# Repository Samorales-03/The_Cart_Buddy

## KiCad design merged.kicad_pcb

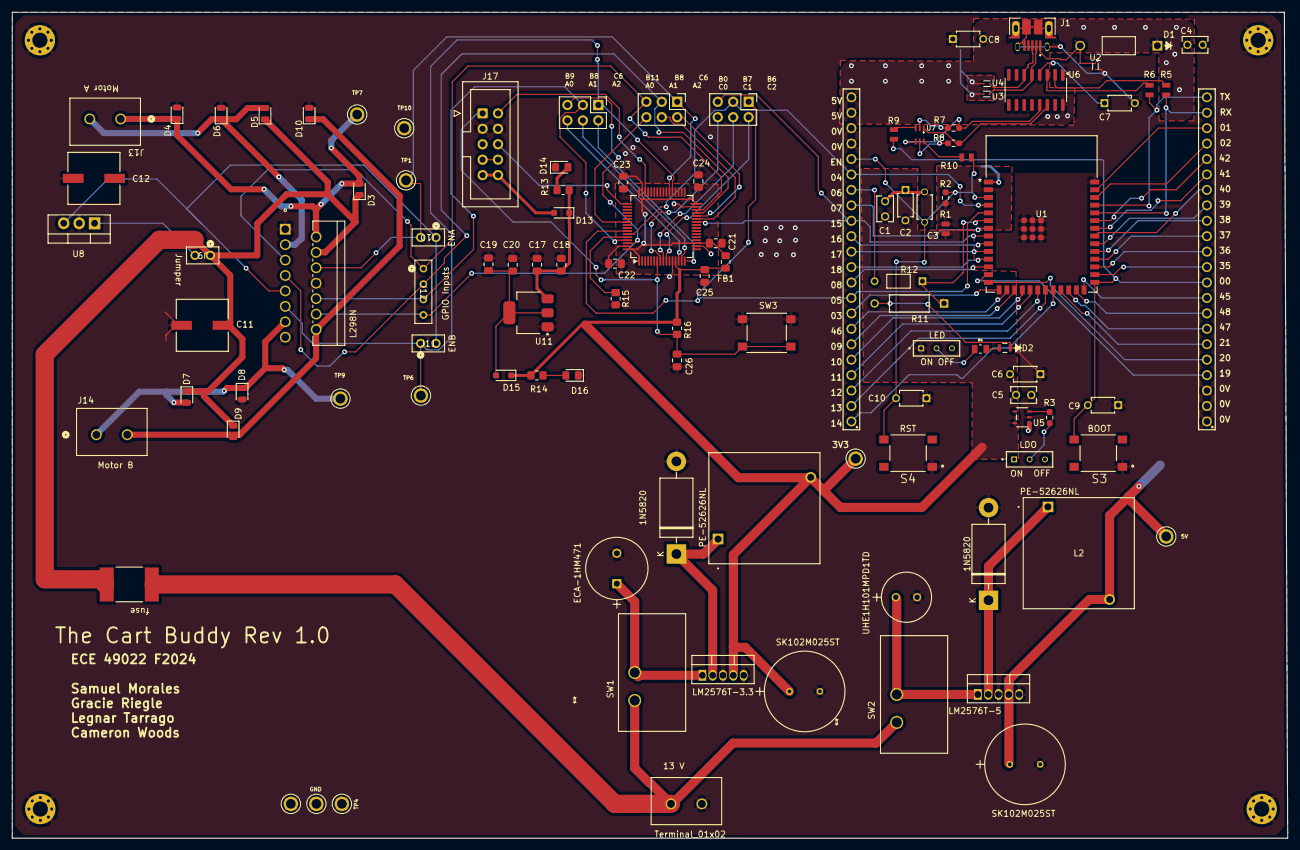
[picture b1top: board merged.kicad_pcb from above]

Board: 2 copper layers, 209.9 x 135.9 mm, 110 parts (0 on the bottom side), 96 nets.

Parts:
C1, C4, C5: 10uF; CAP_FG18_TDK
C2, C6, C7, C8, C9, C10: 0.1uF; K104K10X7RF5UH5_VIS
C3: 1uF; CAPRB500W50L400T250H550
C11, C12: 220 uF; CAP_PC_8X12_NCH
C13: ECA-1HM471; PCAP_10x20_PAN
C14, C16: SK102M025ST; SK102M025ST_CND
C15: UHE1H101MPD1TD; CAP_RN_8X11P5_NCH
C17, C20: 22uF; C_0805_2012Metric_Pad1.18x1.45mm_HandSolder
C18, C19, C21, C22, C23, C24, C25, C26: 0.1uF; C_0805_2012Metric_Pad1.18x1.45mm_HandSolder
CR1: L298N; Multiwatt15_V_STM
D1: 1N5819; CR_DO-41_SDS
D2: LED-red; LED0805N_CML-L
D3, D4, D5, D6, D7, D8, D9, D10: D_0805_2012Metric
D11, D12: 1N5820; D_DO-201AD_P15.24mm_Horizontal
D13, D15: BAT60JFILM; D_SOD-323_HandSoldering
D14, D16: LED; LED_0805_2012Metric_Pad1.15x1.40mm_HandSolder
F1: fuse; 0ZCF_BEL
FB1: FerriteBead; L_0805_2012Metric_Pad1.15x1.40mm_HandSolder
H1, H2, H3, H4: MountingHole_2.5mm_Pad_Via
J1: Micro-USB; AMPHENOL_10103594-0001LF
J2: ON; SAMTEC_TS-103-T-A
J3: LDO; SAMTEC_TS-103-T-A
J4, J5, J16: Conn_02x03_Odd_Even; PinHeader_2x03_P2.54mm_Vertical
J6: LEFT; 61302211121
J7: RIGHT; 61302211121
J9: Jumper; CON2_1X2_TUC_HTS_SAI
J10: ENA; CON2_1X2_TUC_HTS_SAI
J11: ENB; CON2_1X2_TUC_HTS_SAI
J12: GPIO Inputs; CON4_1X4_TU_HTS_SAI
J13: Motor A; CONN_OSTTC022162_OST
J14: Motor B; CONN_OSTTC022162_OST
J15: Terminal_01x02; CONN_OSTTC022162_OST
J17: Conn_02x05_Odd_Even; IDC-Header_2x05_P2.54mm_Vertical
L1, L2: PE-52626NL; IND_PE-526_LOWPROFILE_PUL
R1, R5, R6, R9, R10: 0Ohm; RES_CRCW_0805_VIS-L
R2, R3, R7, R8: 10kOhm; R_0603_1608Metric_Pad0.98x0.95mm_HandSolder
R4: 68Ohm; RESC2012X60N
R11: 3kOhm; STA_CF14_STP
R12: 2kOhm; STA_CF18_STP
R13, R16: 5.1k; R_0805_2012Metric_Pad1.20x1.40mm_HandSolder
R14: 1k; R_0805_2012Metric_Pad1.20x1.40mm_HandSolder
R15: 100k; R_0805_2012Metric_Pad1.20x1.40mm_HandSolder
S3, S4: SW; SW_PTS645SK50SMTR92LFS
SW1, SW2: L101011MS02Q; SW_1MS02Q_CNK
SW3: SW_Push; SW_SPST_PTS645
TP1, TP2, TP3, TP4, TP5, TP6, TP7, TP8, TP9, TP10: 5006; KEYSTONE_5006
U1: ESP32-S3-WROOM-1-N8; ESP32-S3-WROOM-1_EXP
U2, U3, U4: ESD; CPDQ-L
U5: LDO; SOT-25_TOR-L
U6: CH340C; SOIC-16_3.9x9.9mm_P1.27mm
U7: BJT; SOT236
U8: L7805; TO-220-3_Vertical
U9: LM2576T-3.3; TO-220-5_Vertical
U10: LM2576T-5; TO-220-5_Vertical
U11: LD1117S33TR_SOT223; SOT-223-3_TabPin2
U12: STM32F091R_B-C_Tx; LQFP-64_10x10mm_P0.5mm

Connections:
+5V: C17.1, C18.1, D13.1, R13.1, U11.3 (VI)
/DTR: R7.1, U6.13 (~DTR), U7.4
/EN: C3.2, C10.2, J6.18, R2.2, R10.2, S4.4, U1.3 (EN)
/ESP_3V3: R1.2, R2.1, U1.2 (3V3)
/GPIO00: C9.2, J7.10, R9.1, S3.4, U1.27 (IO0)
/GPIO01: J7.20, U1.39 (IO1)
/GPIO02: J7.19, U1.38 (IO2)
/GPIO03: J6.8, U1.15 (IO3)
/GPIO06: R11.1, R12.1, U1.6 (IO6)
/GPIO07: J6.15, U1.7 (IO7)
/GPIO08: J6.10, U1.12 (IO8)
/GPIO09: J6.6, U1.17 (IO9)
/GPIO10: J6.5, U1.18 (IO10)
/GPIO11: J6.4, U1.19 (IO11)
/GPIO12: J6.3, U1.20 (IO12)
/GPIO13: J6.2, U1.21 (IO13)
/GPIO14: J6.1, U1.22 (IO14)
/GPIO16: J6.13, U1.9 (IO16)
/GPIO17: J6.12, U1.10 (IO17)
/GPIO18: J6.11, U1.11 (IO18)
/GPIO19: J7.4, U1.13 (IO19)
/GPIO20: J7.5, U1.14 (IO20)
/GPIO21: J7.6, U1.23 (IO21)
/GPIO35: J7.11, U1.28 (IO35)
/GPIO36: J7.12, U1.29 (IO36)
/GPIO37: J7.13, U1.30 (IO37)
/GPIO38: J7.14, U1.31 (IO38)
/GPIO39: J7.15, U1.32 (IO39)
/GPIO40: J7.16, U1.33 (IO40)
/GPIO41: J7.17, U1.34 (IO41)
/GPIO42: J7.18, U1.35 (IO42)
/GPIO45: J7.9, U1.26 (IO45)
/GPIO46: J6.7, U1.16 (IO46)
/GPIO47: J7.7, U1.24 (IO47)
/GPIO48: J7.8, U1.25 (IO48)
/MOTORA: CR1.2 (OUTPUT_1), D3.2 (A), D4.1 (K), J13.1, TP7.1
/MOTORB: CR1.13 (OUTPUT_3), D7.2 (A), D8.1 (K), J14.1, TP9.1
/RTS: R8.2, U6.14 (~RTS), U7.1
/STM_3V3: C21.1, C22.1, C23.1, C24.1, FB1.1, U12.1 (VBAT), U12.19 (VDD), U12.32 (VDD), U12.48 (VDDIO2), U12.64 (VDD)
/U0RXD: J7.21, R5.2, U1.36 (RXD0)
/U0TXD: J7.22, R6.2, U1.37 (TXD0)
/USB_DN: J1.2 (D-), U3.1, U6.5 (UD+)
/USB_DP: J1.3 (D+), U4.1, U6.6 (UD-)
/VBUS: D1.2, J1.1 (VCC), U2.1
/VCC_3V3: C1.2, C2.2, C5.2, C6.2, C14.1, C25.1, D15.1, FB1.2, J2.01, L1.2, R1.1, R14.1, R16.1, TP2.1, U5.5 (VOUT), U9.4 (FB), U12.13 (VDDA)
/VCC_5V: C4.2, C8.2, C16.1, D1.1, J3.01, J6.21, J6.22, L2.2, TP5.1, U5.1 (VIN), U6.16 (VCC), U10.4 (FB)
/VCC_13V: F1.1, J15.1, SW1.1, SW2.1
/VCC_13V_FUSE: C11.1, CR1.4 (SUPPLY_VOLTAGE_VS), D3.1 (K), D5.1 (K), D7.1 (K), D9.1 (K), F1.2, J9.1
Earth: C1.1, C2.1, C3.1, C4.1, C5.1, C6.1, C7.2, C8.1, C9.1, C10.1, C11.2, C12.2, C13.2, C14.2, C15.2, C16.2, C17.2, C18.2, C19.2, C20.2, C21.2, C22.2, C23.2, C24.2, C25.2, C26.2, CR1.1 (CURRENT_SENSING_A), CR1.8 (GND), CR1.15 (CURRENT_SENSING_B), D2.1 (K), D4.2 (A), D6.2 (A), D8.2 (A), D10.2 (A), D11.2 (A), D12.2 (A), D14.1 (K), D16.1 (K), H1.1, H2.1, H3.1, H4.1, J1.5 (GND), J1.6 (SHIELD), J1.7 (SHIELD__1), J1.8 (SHIELD__2), J1.9 (SHIELD__3), J1.10 (SHIELD__4), J1.11 (SHIELD__5), J1.S1 (SHIELD__6), J1.S2 (SHIELD__7), J6.19, J6.20, J7.1, J7.2, J7.3, J15.2, J17.3, J17.4, R11.2, R15.2, S3.1, S4.1, SW3.1, TP3.1, TP4.1, TP8.1, TP10.1, U1.1 (GND), U1.40 (GND), U1.41 (GND), U1.42 (GND), U1.43 (GND), U1.44 (GND), U1.45 (GND), U1.46 (GND), U1.47 (GND), U1.48 (GND), U1.49 (GND), U2.2, U3.2, U4.2, U5.2 (VSS), U6.1 (GND), U8.2 (GND), U9.3 (GND), U9.5 (~ON/OFF), U10.3 (GND), U10.5 (~ON/OFF), U11.1 (GND), U12.12 (VSSA), U12.18 (VSS), U12.31 (VSS), U12.47 (VSS), U12.63 (VSS)
NRST: C26.1, J17.1, R16.2, SW3.2, U12.7 (NRST)
unnamed: C12.1, CR1.9 (LOGIC_SUPPLY_VOLTAGE_VSS), J10.1, J11.2, U8.3 (OUT)
unnamed: CR1.3 (OUTPUT_2), D5.2 (A), D6.1 (K), J13.2
unnamed: CR1.14 (OUTPUT_4), D9.2 (A), D10.1 (K), J14.2
unnamed: D2.2 (A), R4.1
unnamed: D11.1 (K), L1.1, U9.2 (OUT)
unnamed: D12.1 (K), L2.1, U10.2 (OUT)
unnamed: D14.2 (A), R13.2
unnamed: D16.2 (A), R14.2
unnamed: J2.02, R4.2
unnamed: J3.02, R3.1
unnamed: J6.16, R12.2
unnamed: R7.2, U7.2
unnamed: R8.1, U7.5
unnamed: R9.2, U7.3
unnamed: R10.1, U7.6
unnamed: R3.2, U5.3 (CE)
unnamed: R6.1, U6.3 (RXD)
unnamed: R5.1, U6.2 (TXD)
unnamed: C7.1, U6.4 (V3)
unnamed: J9.2, U8.1 (IN)
unnamed: C13.1, SW1.2, U9.1 (VIN)
unnamed: C15.1, SW2.2, U10.1 (VIN)
unnamed: C19.1, C20.1, D15.2, U11.2 (VO)
PA0: J4.6, U12.14 (PA0)
PA1: J4.4, U12.15 (PA1)
PA2: J4.2, U12.16 (PA2)
PB0: J6.14, J16.5, U1.8 (IO15), U12.26 (PB0)
PB1: J5.4, U12.27 (PB1)
PB2: J5.2, U12.28 (PB2)
PB3: J5.6, U12.55 (PB3)
PB6: J6.9, J16.1, U1.5 (IO5), U12.58 (PB6)
PB7: J6.17, J16.3, U1.4 (IO4), U12.59 (PB7)
PB8: CR1.10 (INPUT_3), J4.3, J12.3, U12.61 (PB8)
PB9: CR1.12 (INPUT_4), J4.5, J12.4, U12.62 (PB9)
PB10: CR1.7 (INPUT_2), J5.3, J12.2, U12.29 (PB10)
PB11: CR1.5 (INPUT_1), J5.5, J12.1, U12.30 (PB11)
PC0: J16.6, U12.8 (PC0)
PC1: J16.4, U12.9 (PC1)
PC2: J16.2, U12.10 (PC2)
PC6: CR1.11 (ENABLE_B), J4.1, J11.1, TP6.1, U12.37 (PC6)
PC7: CR1.6 (ENABLE_A), J5.1, J10.2, TP1.1, U12.38 (PC7)
PF11: R15.1, U12.60 (PF11)
SWCLK_IN: J17.6, U12.49 (PA14)
SWDIO_IN: J17.2, U12.46 (PA13)
U5V: D13.2, J17.9, J17.10
V3.3_IN: J17.7, J17.8

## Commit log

2025-07-26 adding parts
2025-07-26 remove WRONG lub
2025-07-26 adding correct library
